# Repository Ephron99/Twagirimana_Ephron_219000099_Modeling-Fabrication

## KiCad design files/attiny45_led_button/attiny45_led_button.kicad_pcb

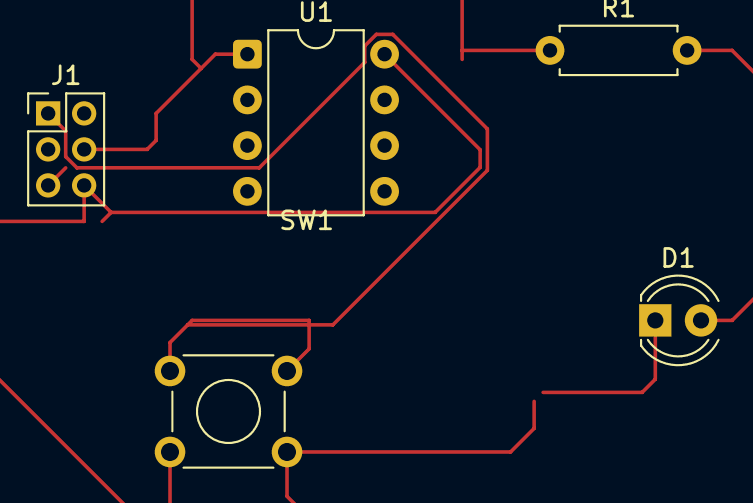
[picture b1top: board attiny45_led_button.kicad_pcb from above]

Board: 2 copper layers, 5 parts (0 on the bottom side), 4 nets.

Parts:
D1: LED; LED_D4.0mm
J1: Conn_02x03_Counter_Clockwise; PinHeader_2x03_P2.00mm_Vertical
R1: R; R_Axial_DIN0207_L6.3mm_D2.5mm_P7.62mm_Horizontal
SW1: SW_Push; SW_TH_Tactile_Omron_B3F-102x
U1: ATtiny45-20M; DIP-8_W7.62mm

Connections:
GND: D1.1 (K), J1.6, SW1.2, U1.8 (GND)
unnamed: D1.2 (A), R1.2
unnamed: J1.1, SW1.1
unnamed: J1.4, J1.5, R1.1, U1.1 (~RESET/PB5)

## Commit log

2026-02-03 Deployed a565972 with MkDocs version: 1.6.1
2026-03-25 Initial commit for MkDocs documentation
2026-03-25 Deployed 7682a95 with MkDocs version: 1.6.1
2026-03-25 update docs
2026-03-25 Deployed 7651e55 with MkDocs version: 1.6.1
2026-03-30 day3
2026-03-30 Deployed 27e7dc5 with MkDocs version: 1.6.1
2026-04-02 with day3
2026-04-02 Deployed 6b8f36f with MkDocs version: 1.6.1
2026-04-02 with on day3
2026-04-02 Deployed 375f750 with MkDocs version: 1.6.1
2026-04-02 with update
2026-04-02 Deployed 8823698 with MkDocs version: 1.6.1
